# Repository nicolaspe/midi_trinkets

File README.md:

# midi_trinkets
experimental small MIDI creations

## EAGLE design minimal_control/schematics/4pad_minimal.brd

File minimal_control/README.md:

MIDI controller created for use in conjunction with my [Rhythmic Skin] project

board modified from [MBennetts custom board](https://oshpark.com/shared_projects/FmtT6vg8)

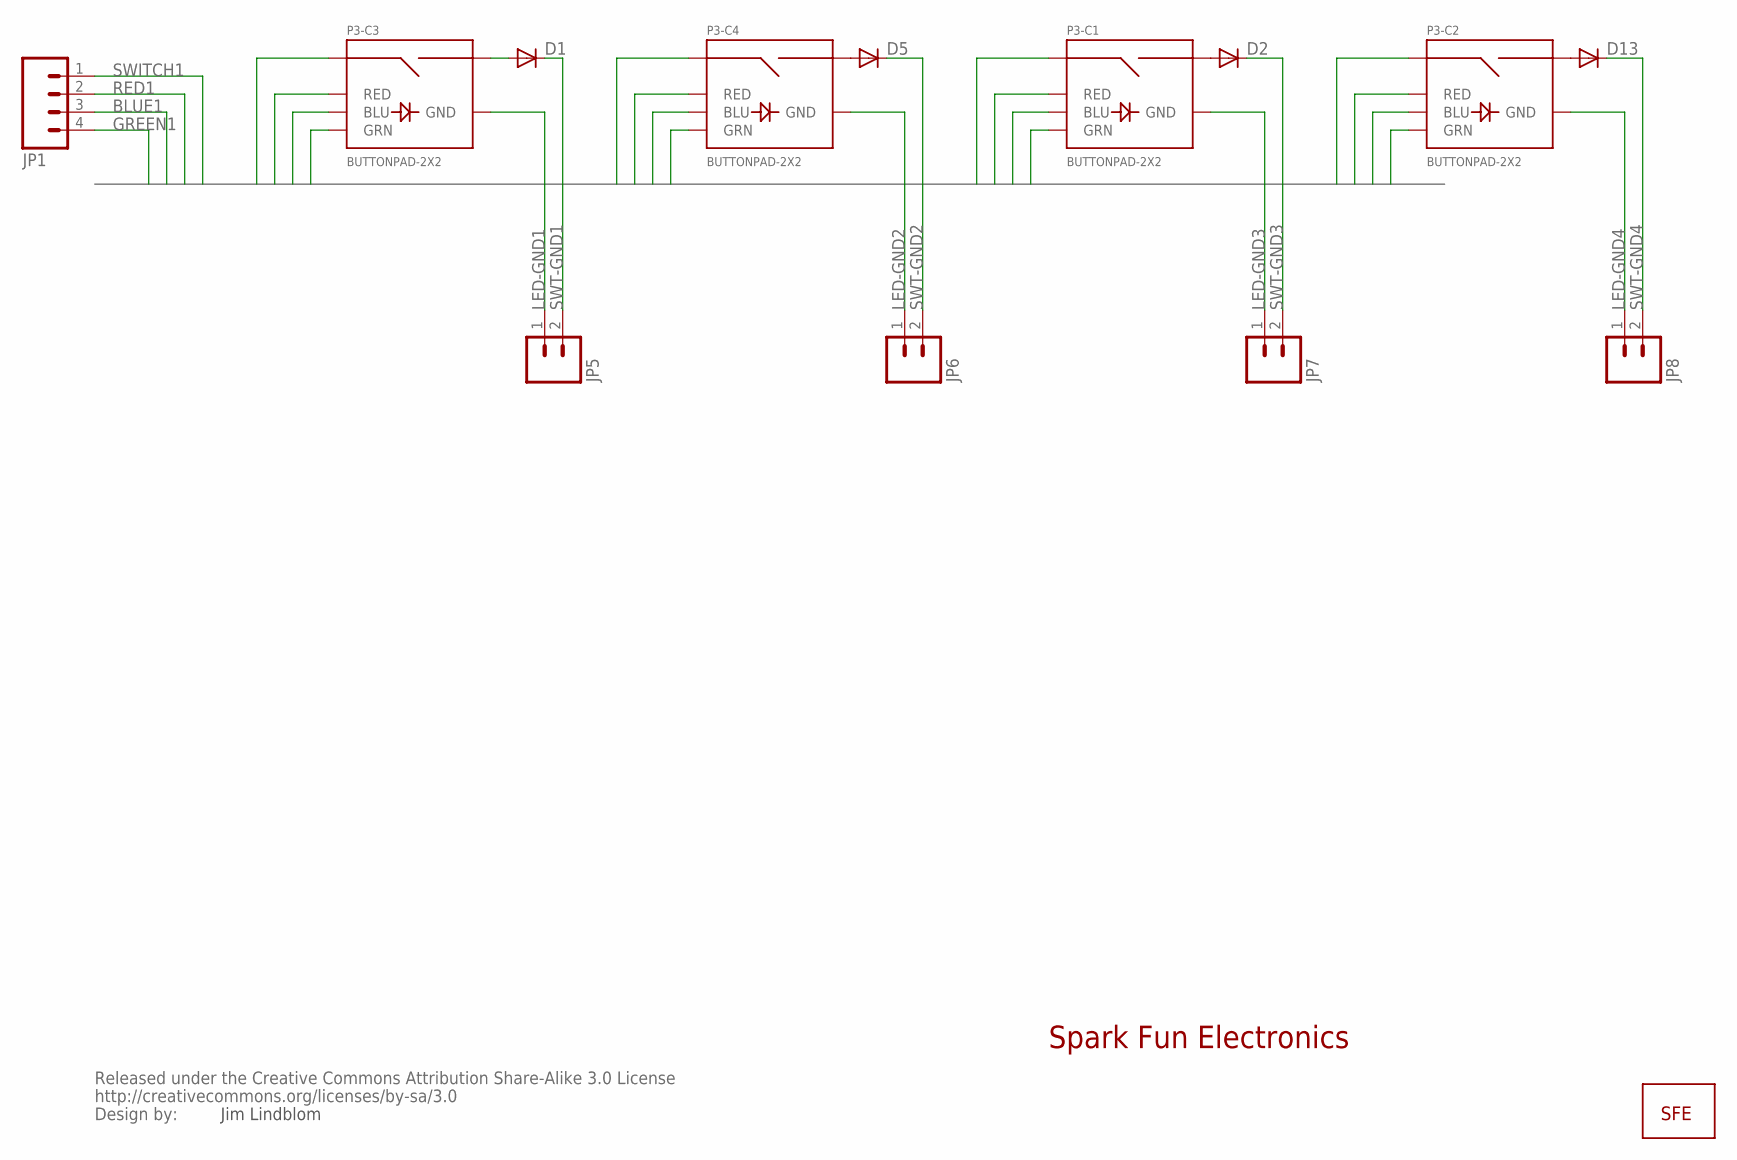
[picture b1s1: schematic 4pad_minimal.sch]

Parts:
D1, D2, D5, D13: DIODE-1N4148; DOIDE-1N4148
JP1: M04POLAR; MOLEX-1X4
JP5, JP6, JP7, JP8: M02POLAR; MOLEX-1X2
P3: BUTTONPAD-2X2
U$1: LOGO-SFENEW; SFE-NEW-WEBLOGO
U$2: CREATIVE_COMMONS

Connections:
BLUE1: JP1.3, P3.BLU1 (BLU), P3.BLU2 (BLU), P3.BLU3 (BLU), P3.BLU4 (BLU)
GREEN1: JP1.4, P3.GRN1 (GRN), P3.GRN2 (GRN), P3.GRN3 (GRN), P3.GRN4 (GRN)
LED-GND1: JP5.1, P3.GND3 (GND)
LED-GND2: JP6.1, P3.GND4 (GND)
LED-GND3: JP7.1, P3.GND1 (GND)
LED-GND4: JP8.1, P3.GND2 (GND)
unnamed: D1.P$1 (A), P3.SIG6 (SIG2)
unnamed: D2.P$1 (A), P3.SIG2
unnamed: D13.P$1 (A), P3.SIG4 (SIG2)
unnamed: D5.P$1 (A), P3.SIG8 (SIG2)
RED1: JP1.2, P3.RED1 (RED), P3.RED2 (RED), P3.RED3 (RED), P3.RED4 (RED)
SWITCH1: JP1.1, P3.SIG1, P3.SIG3 (SIG1), P3.SIG5 (SIG1), P3.SIG7 (SIG1)
SWT-GND1: D1.P$2 (C), JP5.2
SWT-GND2: D5.P$2 (C), JP6.2
SWT-GND3: D2.P$2 (C), JP7.2
SWT-GND4: D13.P$2 (C), JP8.2

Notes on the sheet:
Spark Fun Electronics
Jim Lindblom

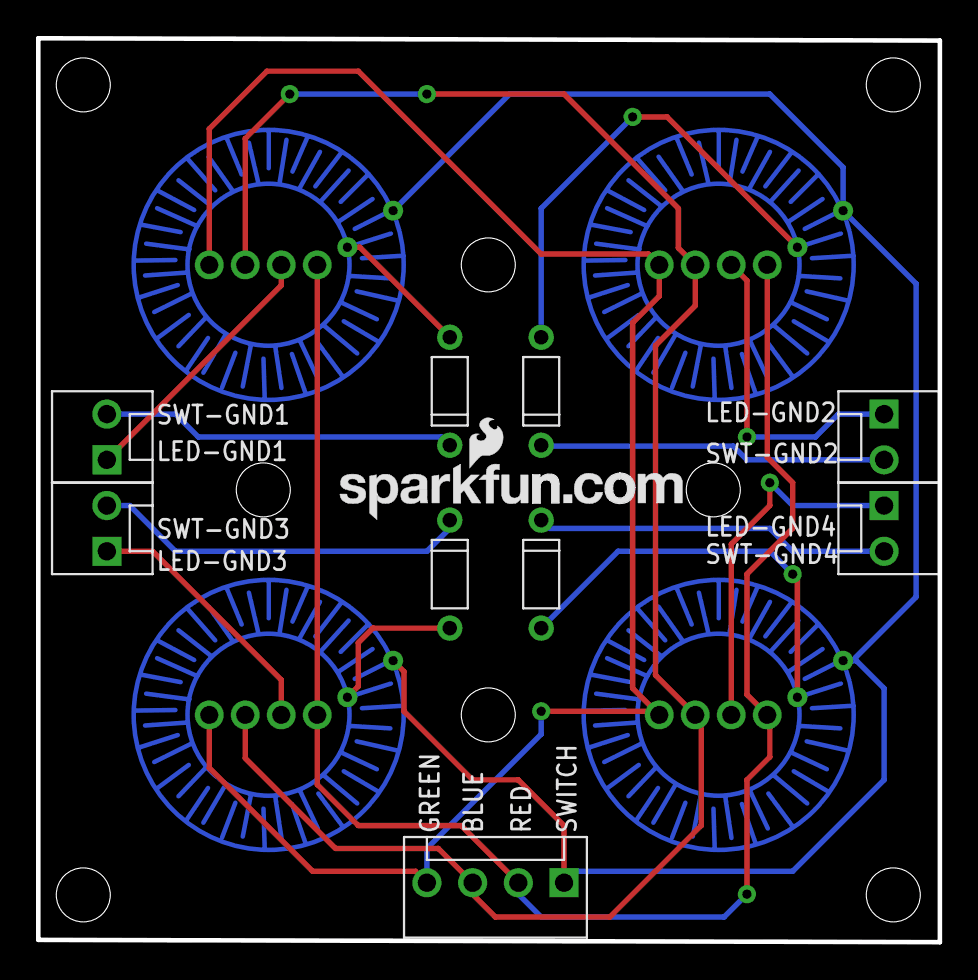
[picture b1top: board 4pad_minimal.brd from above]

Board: 2 copper layers, 50.1 x 50.2 mm, 12 parts (1 on the bottom side), 16 nets.

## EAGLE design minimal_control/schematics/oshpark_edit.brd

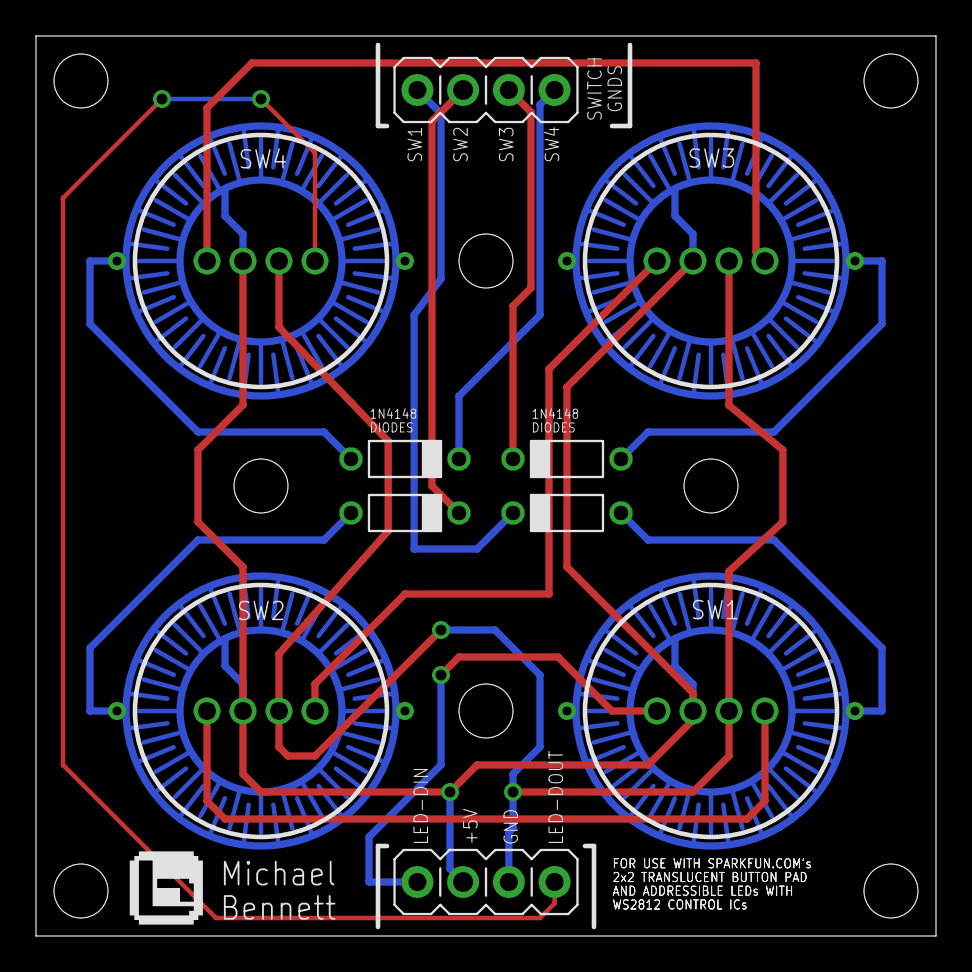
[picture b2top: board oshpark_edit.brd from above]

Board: 2 copper layers, 50.0 x 50.0 mm, 10 parts (0 on the bottom side), 15 nets.

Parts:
C1, C2, C3, C4: 2X2_BUTTON_RGB_ADDR
U$1, U$2, U$3, U$4: 1N4148; 1N4181
U$5, U$6: JUMPER4X1; J4X1

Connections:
unnamed: C1.GND, C2.GND, C3.GND, C4.GND, U$5.P$3
unnamed: C3.SWGND2, U$2.P$1
unnamed: C4.SWGND1, U$1.P$1
unnamed: C1.VDD, C2.VDD, C3.VDD, C4.VDD, U$5.P$2
unnamed: C2.SWGND1, U$3.P$1
unnamed: C1.SWGND2, U$4.P$1
unnamed: C1.DIN, U$5.P$1
unnamed: C4.DOUT, U$5.P$4
unnamed: U$4.P$2, U$6.P$1
unnamed: U$3.P$2, U$6.P$2
unnamed: U$2.P$2, U$6.P$3
unnamed: U$1.P$2, U$6.P$4
SIG2: C1.DOUT, C2.DIN
SIG3: C2.DOUT, C3.DIN
SIG4: C3.DOUT, C4.DIN

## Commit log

2018-08-26 1blaster v0.0.1
2018-09-11 1blaster complete
2018-09-14 add schematics
2018-09-15 schematics update for milling stabillity

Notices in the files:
parts and their libraries:
SparkFun: Released under the Creative Commons Attribution Share-Alike 3.0 License
SparkFun: http://creativecommons.org/licenses/by-sa/3.0
